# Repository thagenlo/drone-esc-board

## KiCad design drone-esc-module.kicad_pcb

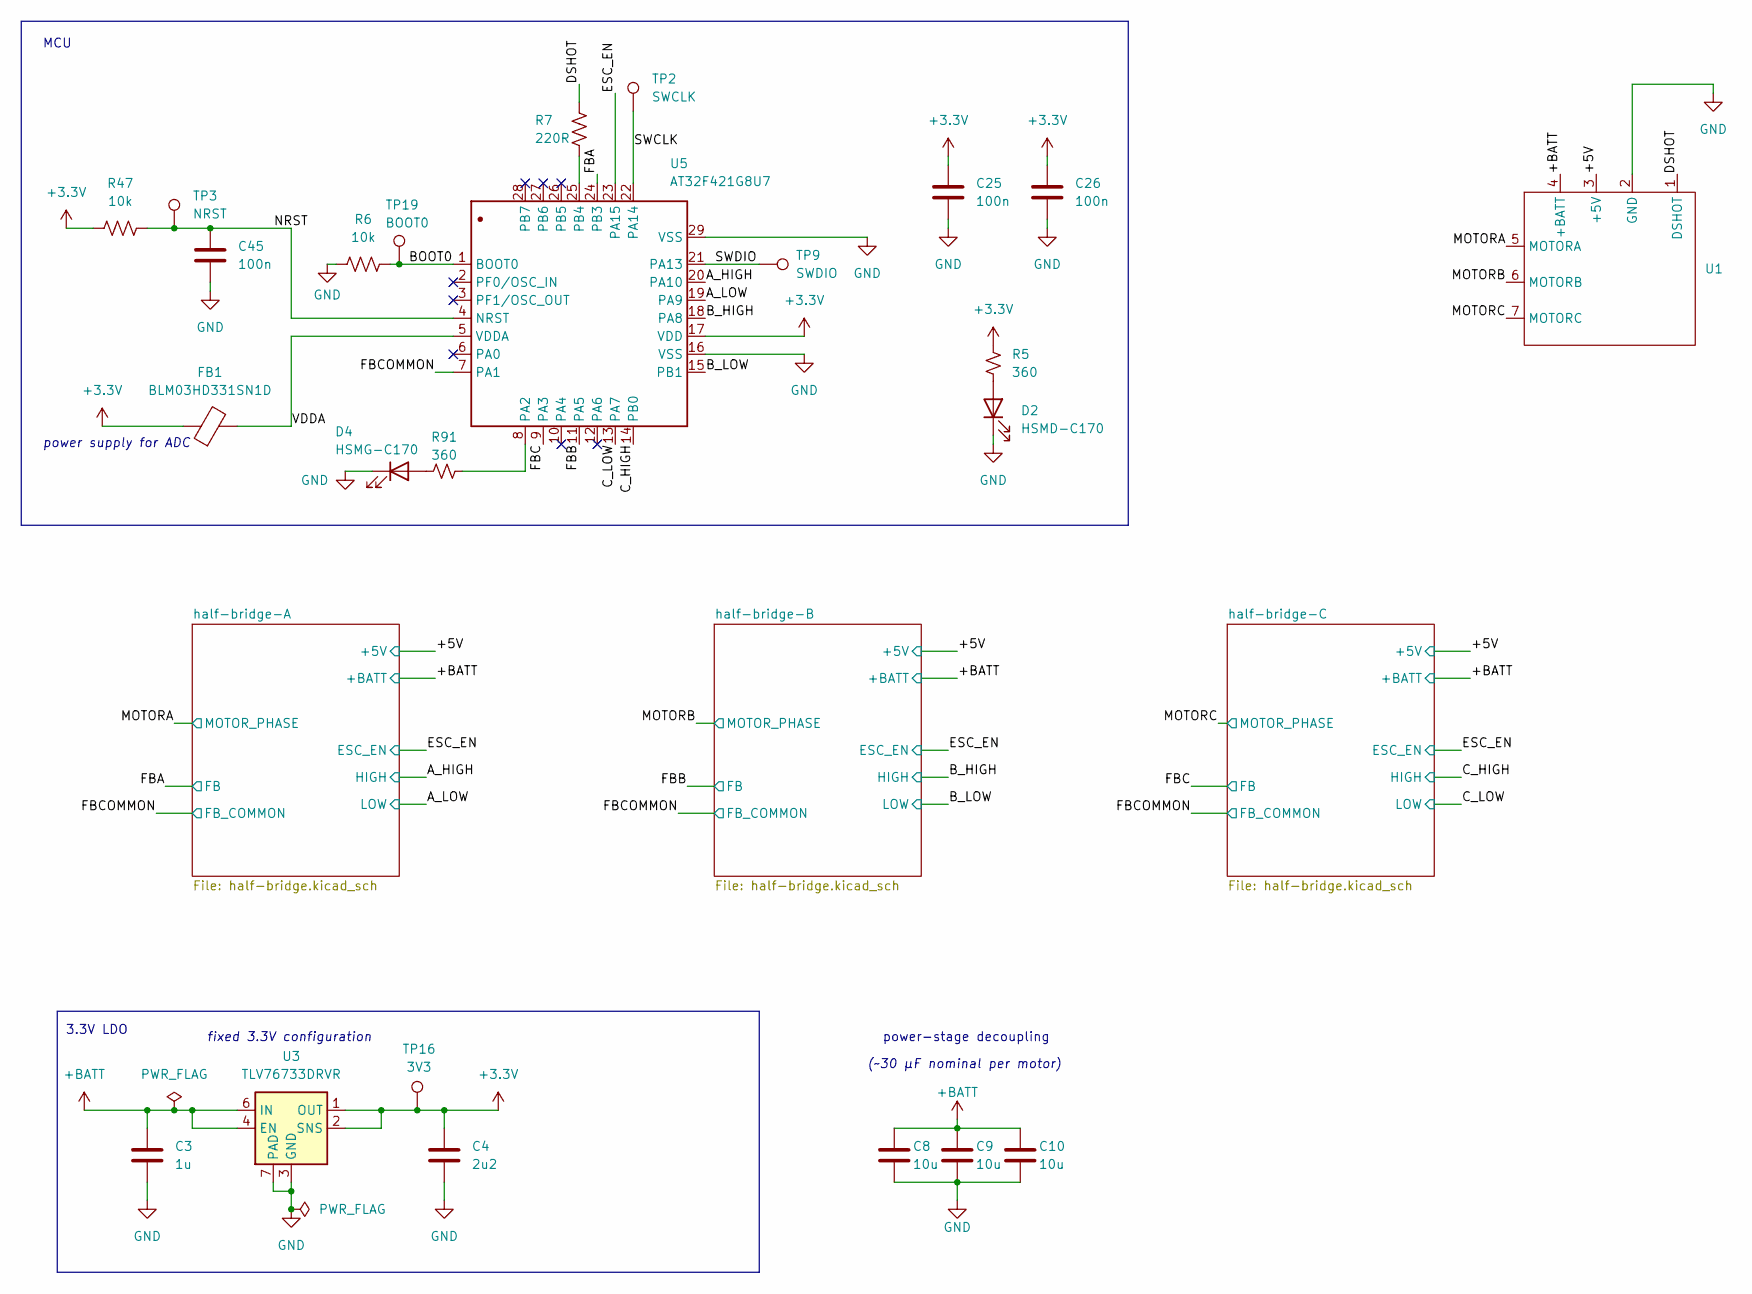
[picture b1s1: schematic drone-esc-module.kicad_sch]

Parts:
C3: 1u; C_0201_0603Metric
C4: 2u2; C_0201_0603Metric
C8, C9, C10: 10u; C_0805_2012Metric
C25, C26, C45: 100n; C_0201_0603Metric
D2: HSMD-C170; LED_0805_2012Metric
D4: HSMG-C170; LED_0805_2012Metric
FB1: BLM03HD331SN1D; R_0201_0603Metric
R5, R91: 360; R_0201_0603Metric
R6, R47: 10k; R_0201_0603Metric
R7: 220R; R_0201_0603Metric
TP2: SWCLK; TestPoint_Pad_D1.0mm
TP3: NRST; TestPoint_Pad_D1.0mm
TP9: SWDIO; TestPoint_Pad_D1.0mm
TP16: 3V3; TestPoint_Pad_D1.0mm
TP19: BOOT0; TestPoint_Pad_D1.0mm
U1: esc-module-board
U3: TLV76733DRVR; WSON-6-1EP_2x2mm_P0.65mm_EP1x1.6mm_ThermalVias
U5: AT32F421G8U7; QFN-28-1EP_4x4mm_P0.45mm_EP2.4x2.4mm; Manufacturer Part AT32F421G8U7

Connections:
+3.3V: C4.1, C25.1, C26.1, FB1.1, R5.1, R47.1, TP16.1 (1_1), U3.1 (OUT), U3.2 (SNS), U5.17 (VDD)
+BATT: C3.1, C8.1, C9.1, C10.1, U1.4 (+BATT), U3.4 (EN), U3.6 (IN); also elsewhere on the board
/+5V: U1.3 (+5V); also elsewhere on the board
/A_HIGH: U5.20 (PA10); also elsewhere on the board
/A_LOW: U5.19 (PA9); also elsewhere on the board
/BOOT0: R6.2, TP19.1 (1_1), U5.1 (BOOT0)
/B_HIGH: U5.18 (PA8); also elsewhere on the board
/B_LOW: U5.15 (PB1); also elsewhere on the board
/C_HIGH: U5.14 (PB0); also elsewhere on the board
/C_LOW: U5.13 (PA7); also elsewhere on the board
/DSHOT: R7.2, U1.1 (DSHOT)
/ESC_EN: U5.23 (PA15); also elsewhere on the board
/FBA: U5.24 (PB3); also elsewhere on the board
/FBB: U5.11 (PA5); also elsewhere on the board
/FBC: U5.9 (PA3); also elsewhere on the board
/FBCOMMON: U5.7 (PA1); also elsewhere on the board
/MOTORA: U1.5 (MOTORA); also elsewhere on the board
/MOTORB: U1.6 (MOTORB); also elsewhere on the board
/MOTORC: U1.7 (MOTORC); also elsewhere on the board
/NRST: C45.1, R47.2, TP3.1 (1_1), U5.4 (NRST)
/SWCLK: TP2.1 (1_1), U5.22 (PA14)
/SWDIO: TP9.1 (1_1), U5.21 (PA13)
/VDDA: FB1.2, U5.5 (VDDA)
GND: C3.2, C4.2, C8.2, C9.2, C10.2, C25.2, C26.2, C45.2, D2.1 (K), D4.1 (K), R6.1, U1.2 (GND), U3.3 (GND), U3.5 (GND), U3.7 (PAD), U5.16 (VSS), U5.29 (VSS); also elsewhere on the board
unnamed: D2.2 (A), R5.2
unnamed: D4.2 (A), R91.2
unnamed: R91.1, U5.8 (PA2)
unnamed: R7.1, U5.25 (PB4)

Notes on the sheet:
power-stage decoupling
MCU
3.3V LDO
power supply for ADC
fixed 3.3V configuration
(~30 µF nominal per motor)

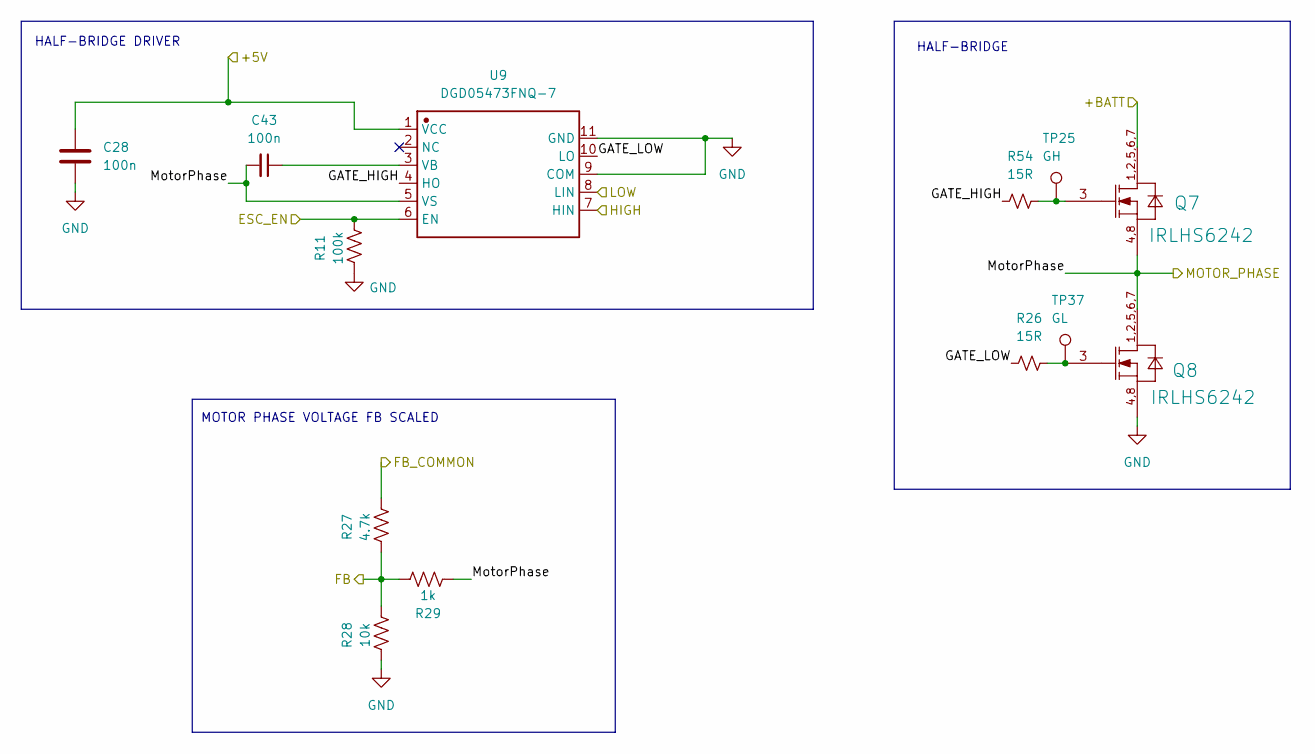
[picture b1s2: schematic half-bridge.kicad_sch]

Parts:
C28, C43: 100n; C_0201_0603Metric
Q7, Q8: IRLHS6242; IRL100HS121-V
R11: 100k; R_0201_0603Metric
R26, R54: 15R; R_0201_0603Metric
R27: 4.7k; R_0201_0603Metric
R28: 10k; R_0201_0603Metric
R29: 1k; R_0201_0603Metric
TP25: GH; TestPoint_Pad_D1.0mm
TP37: GL; TestPoint_Pad_D1.0mm
U9: DGD05473FNQ-7; DFN-10-1EP_3x3mm_P0.5mm_EP1.7x2.5mm; Manufacturer Part DGD05473FNQ-7

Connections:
+BATT: Q7.1 (DRAIN1), Q7.2 (DRAIN2), Q7.5 (DRAIN3), Q7.6 (DRAIN4), Q7.7 (DRAIN5); also elsewhere on the board
/+5V: C28.1, U9.1 (VCC); also elsewhere on the board
/A_HIGH: U9.7 (HIN); also elsewhere on the board
/A_LOW: U9.8 (LIN); also elsewhere on the board
/ESC_EN: R11.1, U9.6 (EN); also elsewhere on the board
/FBA: R27.2, R28.1, R29.1; also elsewhere on the board
/FBCOMMON: R27.1; also elsewhere on the board
/MOTORA: C43.2, Q7.4 (SOURCE1), Q7.8 (SOURCE2), Q8.1 (DRAIN1), Q8.2 (DRAIN2), Q8.5 (DRAIN3), Q8.6 (DRAIN4), Q8.7 (DRAIN5), R29.2, U9.5 (VS); also elsewhere on the board
/half-bridge-A/GATE_HIGH: R54.1, U9.4 (HO)
/half-bridge-A/GATE_LOW: R26.1, U9.10 (LO)
GND: C28.2, Q8.4 (SOURCE1), Q8.8 (SOURCE2), R11.2, R28.2, U9.9 (COM), U9.11 (GND); also elsewhere on the board
unnamed: Q7.3 (GATE), R54.2, TP25.1 (1_1)
unnamed: Q8.3 (GATE), R26.2, TP37.1 (1_1)
unnamed: C43.1, U9.3 (VB)

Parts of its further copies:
C29, C30, C44, C46: 100n; C_0201_0603Metric
Q9, Q10, Q11, Q12: IRLHS6242; IRL100HS121-V
R12, R13: 100k; R_0201_0603Metric
R30, R34: 4.7k; R_0201_0603Metric
R31, R35: 10k; R_0201_0603Metric
R32, R36: 1k; R_0201_0603Metric
R33, R37, R55, R56: 15R; R_0201_0603Metric
TP26, TP27: GH; TestPoint_Pad_D1.0mm
TP38, TP39: GL; TestPoint_Pad_D1.0mm
U10, U11: DGD05473FNQ-7; DFN-10-1EP_3x3mm_P0.5mm_EP1.7x2.5mm; Manufacturer Part DGD05473FNQ-7

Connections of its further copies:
+BATT: Q9.1 (DRAIN1), Q9.2 (DRAIN2), Q9.5 (DRAIN3), Q9.6 (DRAIN4), Q9.7 (DRAIN5), Q11.1 (DRAIN1), Q11.2 (DRAIN2), Q11.5 (DRAIN3), Q11.6 (DRAIN4), Q11.7 (DRAIN5); also elsewhere on the board
/+5V: C29.1, C30.1, U10.1 (VCC), U11.1 (VCC); also elsewhere on the board
/B_HIGH: U10.7 (HIN); also elsewhere on the board
/B_LOW: U10.8 (LIN); also elsewhere on the board
/C_HIGH: U11.7 (HIN); also elsewhere on the board
/C_LOW: U11.8 (LIN); also elsewhere on the board
/ESC_EN: R12.1, R13.1, U10.6 (EN), U11.6 (EN); also elsewhere on the board
/FBB: R30.2, R31.1, R32.1; also elsewhere on the board
/FBC: R34.2, R35.1, R36.1; also elsewhere on the board
/FBCOMMON: R30.1, R34.1; also elsewhere on the board
/MOTORB: C44.2, Q9.4 (SOURCE1), Q9.8 (SOURCE2), Q10.1 (DRAIN1), Q10.2 (DRAIN2), Q10.5 (DRAIN3), Q10.6 (DRAIN4), Q10.7 (DRAIN5), R32.2, U10.5 (VS); also elsewhere on the board
/MOTORC: C46.2, Q11.4 (SOURCE1), Q11.8 (SOURCE2), Q12.1 (DRAIN1), Q12.2 (DRAIN2), Q12.5 (DRAIN3), Q12.6 (DRAIN4), Q12.7 (DRAIN5), R36.2, U11.5 (VS); also elsewhere on the board
/half-bridge-B/GATE_HIGH: R55.1, U10.4 (HO)
/half-bridge-B/GATE_LOW: R33.1, U10.10 (LO)
/half-bridge-C/GATE_HIGH: R56.1, U11.4 (HO)
/half-bridge-C/GATE_LOW: R37.1, U11.10 (LO)
GND: C29.2, C30.2, Q10.4 (SOURCE1), Q10.8 (SOURCE2), Q12.4 (SOURCE1), Q12.8 (SOURCE2), R12.2, R13.2, R31.2, R35.2, U10.9 (COM), U10.11 (GND), U11.9 (COM), U11.11 (GND); also elsewhere on the board
unnamed: Q9.3 (GATE), R55.2, TP26.1 (1_1)
unnamed: Q10.3 (GATE), R33.2, TP38.1 (1_1)
unnamed: Q11.3 (GATE), R56.2, TP27.1 (1_1)
unnamed: Q12.3 (GATE), R37.2, TP39.1 (1_1)
unnamed: C44.1, U10.3 (VB)
unnamed: C46.1, U11.3 (VB)

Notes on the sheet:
HALF-BRIDGE DRIVER
MOTOR PHASE VOLTAGE FB SCALED
HALF-BRIDGE

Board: 2 copper layers, 63 parts (0 on the bottom side), 43 nets, no tracks yet.

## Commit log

2026-05-01 finish schematic + footprints
2026-05-01 done with schematic fr
